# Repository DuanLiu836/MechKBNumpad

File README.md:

# Custom Mechanical Keyboard Numpad Designed Using KiCad.

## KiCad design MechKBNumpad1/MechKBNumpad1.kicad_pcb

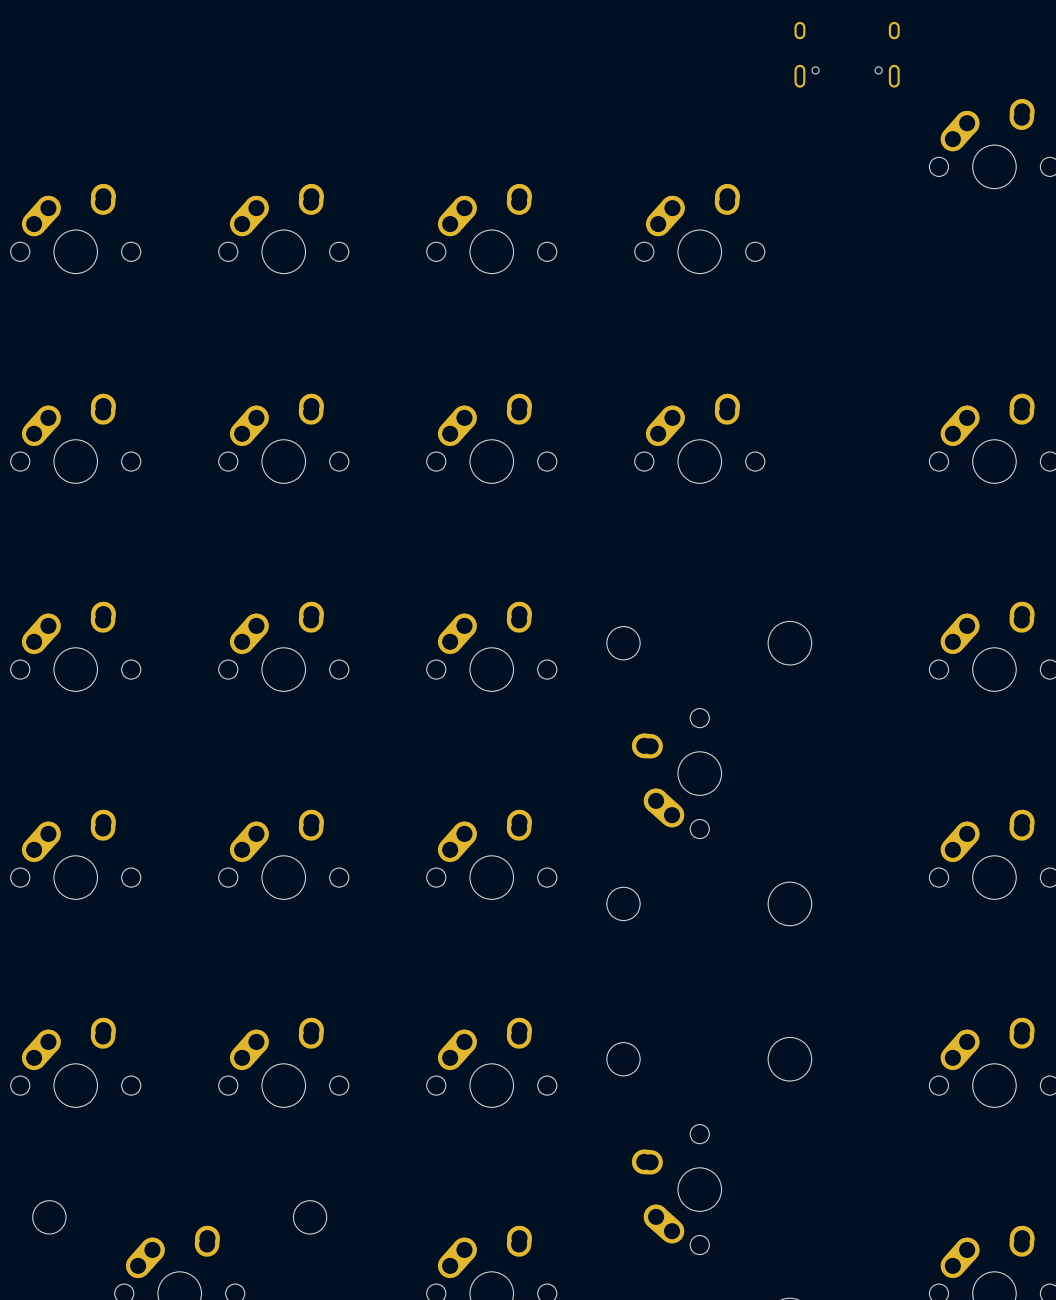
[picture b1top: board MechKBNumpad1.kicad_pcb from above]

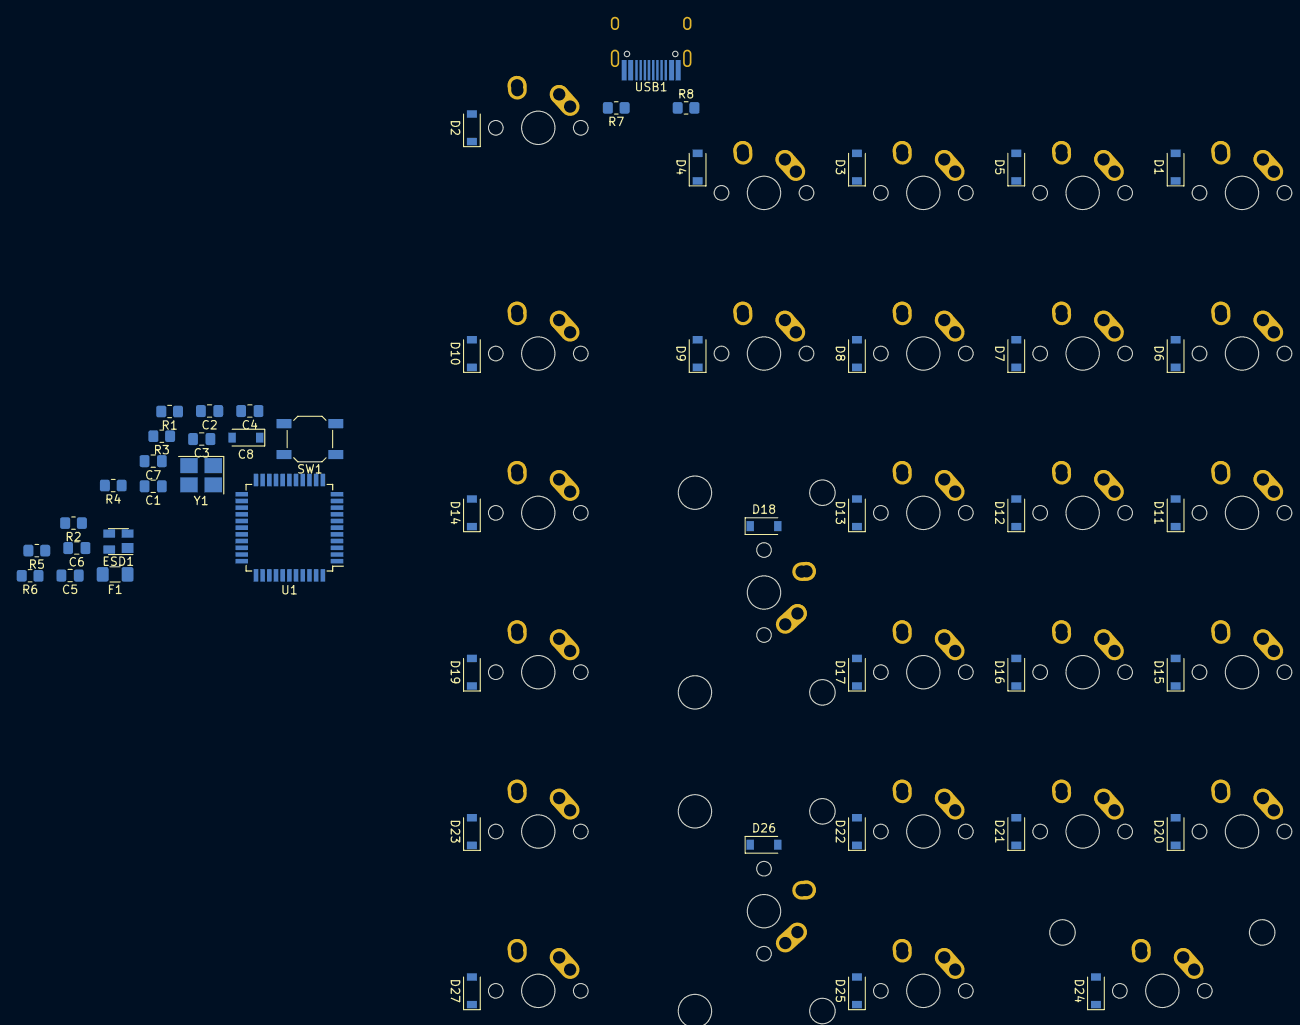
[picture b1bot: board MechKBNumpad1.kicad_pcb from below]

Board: 2 copper layers, 76 parts (49 on the bottom side), 54 nets, no tracks yet.

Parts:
C1, C2, C7: 4.7u; C_0805_2012Metric_Pad1.18x1.45mm_HandSolder
C3, C4, C5, C6: 0.1u; C_0805_2012Metric_Pad1.18x1.45mm_HandSolder
C8: 1u; D_SOD-123
D1, D2, D3, D4, D5, D6, D7, D8, D9, D10, D11, D12, D13, D14, D15, D16, D17, D18, D19, D20, D21, D22, D23, D24, D25, D26, D27: D; D_SOD-123
ESD1: PRTR5V0U2X; SOT-143
F1: 500mA; Fuse_1206_3216Metric_Pad1.42x1.75mm_HandSolder
MX1: play/pause; MX-1U-NoLED
MX2: stop; MX-1U-NoLED
MX3: prev; MX-1U-NoLED
MX4: next; MX-1U-NoLED
MX5: encoder; MX-1U-NoLED
MX6: num lock; MX-1U-NoLED
MX7: /; MX-1U-NoLED
MX8: *; MX-1U-NoLED
MX9: -; MX-1U-NoLED
MX10: mute; MX-1U-NoLED
MX11: 7; MX-1U-NoLED
MX12: 8; MX-1U-NoLED
MX13: 9; MX-1U-NoLED
MX14: macro1; MX-1U-NoLED
MX15: 4; MX-1U-NoLED
MX16: 5; MX-1U-NoLED
MX17: 6; MX-1U-NoLED
MX18: +; MX-2U-NoLED
MX19: macro2; MX-1U-NoLED
MX20: 1; MX-1U-NoLED
MX21: 2; MX-1U-NoLED
MX22: 3; MX-1U-NoLED
MX23: macro3; MX-1U-NoLED
MX24: 0; MX-2U-NoLED
MX25: . del; MX-1U-NoLED
MX26: enter; MX-2U-NoLED
MX27: macro4; MX-1U-NoLED
R1: 10k; R_0805_2012Metric_Pad1.20x1.40mm_HandSolder
R2: 10K; R_0805_2012Metric_Pad1.20x1.40mm_HandSolder
R3, R4, R5, R6: 22; R_0805_2012Metric_Pad1.20x1.40mm_HandSolder
R7, R8: 5.1K; R_0805_2012Metric_Pad1.20x1.40mm_HandSolder
SW1: SW_Push; SW_SPST_SKQG_WithStem
U1: ATmega32U4-AU; TQFP-44_10x10mm_P0.8mm
USB1: HRO-TYPE-C-31-M-12; HRO-TYPE-C-31-M-12-HandSoldering
Y1: Crystal_GND24_Small; Crystal_SMD_3225-4Pin_3.2x2.5mm_HandSoldering

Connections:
+5V: C3.1, C4.1, C5.1, C6.1, C7.1, F1.1, R1.1, U1.2, U1.7, U1.14, U1.24, U1.34, U1.44
D+: R3.1, R6.1
D-: R4.2, R5.2
GND: C1.1, C2.1, C3.2, C4.2, C5.2, C6.2, C7.2, C8.2, ESD1.1, R2.2, R7.2, R8.2, SW1.1, U1.5, U1.15, U1.23, U1.35, U1.43, USB1.1, USB1.12, USB1.13, Y1.2, Y1.4
unnamed: C1.2, U1.17, Y1.1
unnamed: C2.2, U1.16, Y1.3
unnamed: C8.1, U1.6
unnamed: D1.2, MX1.2
unnamed: D2.2, MX2.2
unnamed: D3.2, MX3.2
unnamed: D4.2, MX4.2
unnamed: D5.2, MX5.2
unnamed: D6.2, MX6.2
unnamed: D7.2, MX7.2
unnamed: D8.2, MX8.2
unnamed: D9.2, MX9.2
unnamed: D10.2, MX10.2
unnamed: D11.2, MX11.2
unnamed: D12.2, MX12.2
unnamed: D13.2, MX13.2
unnamed: D14.2, MX14.2
unnamed: D15.2, MX15.2
unnamed: D16.2, MX16.2
unnamed: D17.2, MX17.2
unnamed: D18.2, MX18.2
unnamed: D19.2, MX19.2
unnamed: D20.2, MX20.2
unnamed: D21.2, MX21.2
unnamed: D22.2, MX22.2
unnamed: D23.2, MX23.2
unnamed: D24.2, MX24.2
unnamed: D25.2, MX25.2
unnamed: D26.2, MX26.2
unnamed: D27.2, MX27.2
unnamed: ESD1.2, R6.2, USB1.6, USB1.8
unnamed: ESD1.3, R5.1, USB1.5, USB1.7
unnamed: R1.2, SW1.2, U1.13
unnamed: R2.1, U1.33
unnamed: R3.2, U1.4
unnamed: R4.1, U1.3
unnamed: R7.1, USB1.4
unnamed: R8.1, USB1.10
VCC: F1.2, USB1.2, USB1.11
col0: MX1.1, MX6.1, MX11.1, MX15.1, MX20.1, MX24.1
col1: MX2.1, MX7.1, MX12.1, MX16.1, MX21.1
col2: MX3.1, MX8.1, MX13.1, MX17.1, MX22.1, MX25.1
col3: MX4.1, MX9.1, MX18.1, MX26.1
col4: MX5.1, MX10.1, MX14.1, MX19.1, MX23.1, MX27.1
row0: D1.1, D2.1, D3.1, D4.1, D5.1
row1: D6.1, D7.1, D8.1, D9.1, D10.1
row2: D11.1, D12.1, D13.1, D14.1
row3: D15.1, D16.1, D17.1, D18.1, D19.1
row4: D20.1, D21.1, D22.1, D23.1
row5: D24.1, D25.1, D26.1, D27.1
